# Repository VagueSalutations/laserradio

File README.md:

this is a test
If you can read this, Ian can access the repo

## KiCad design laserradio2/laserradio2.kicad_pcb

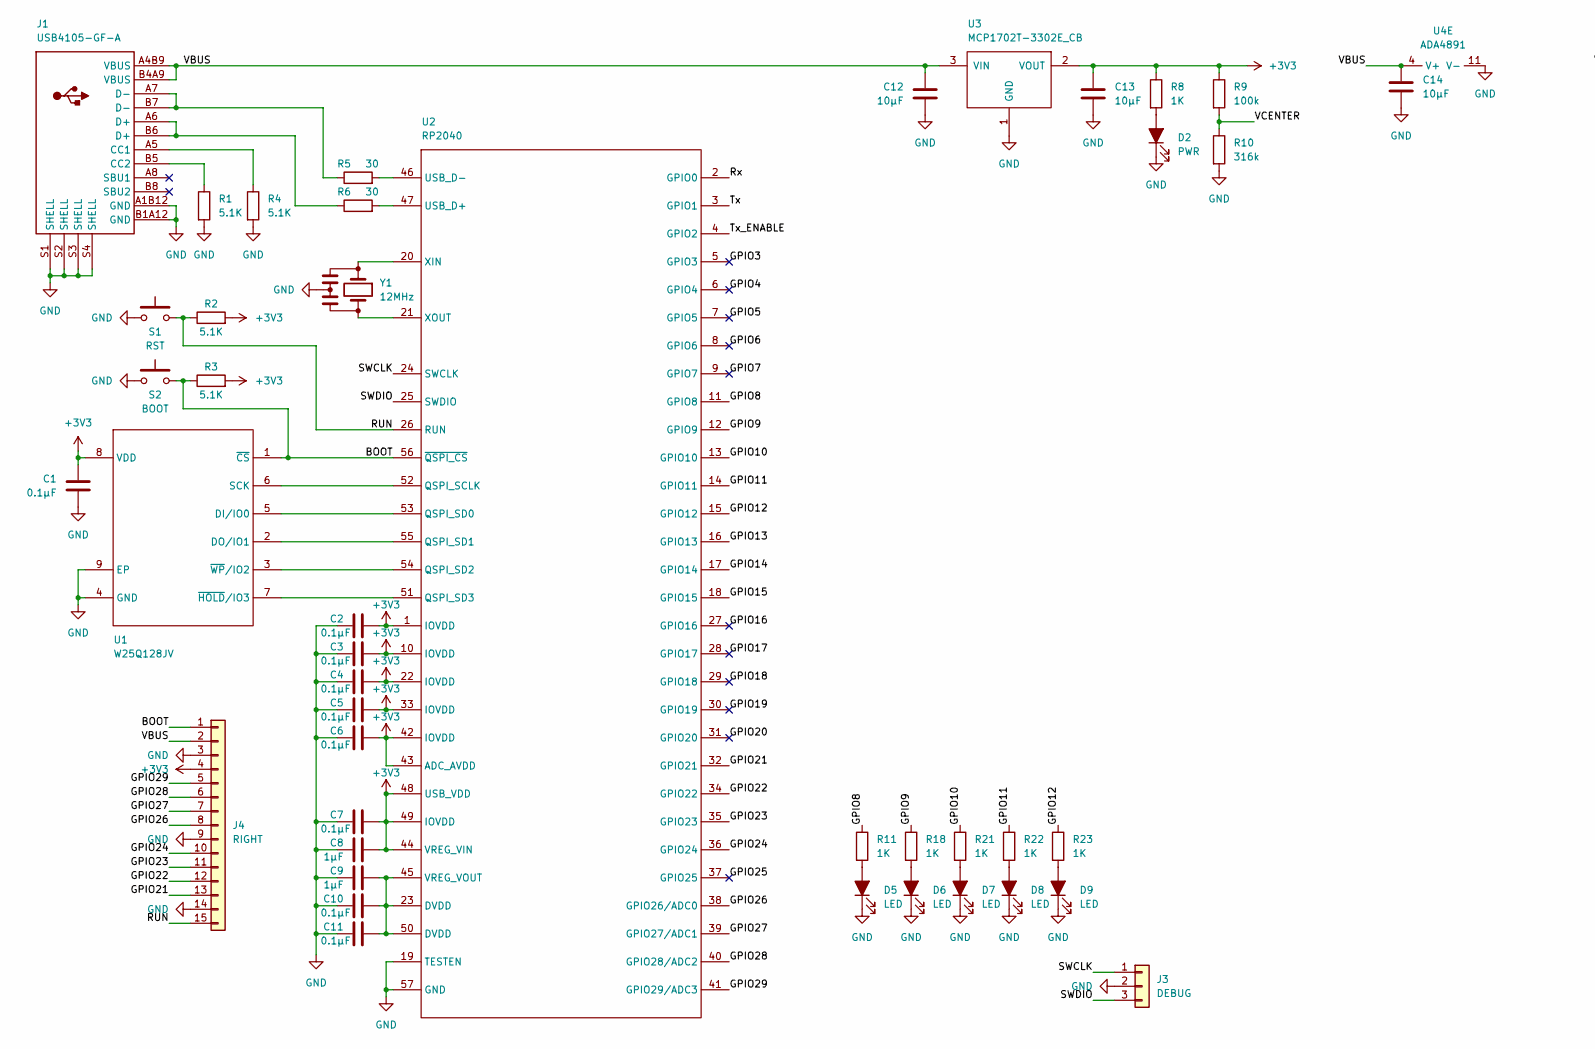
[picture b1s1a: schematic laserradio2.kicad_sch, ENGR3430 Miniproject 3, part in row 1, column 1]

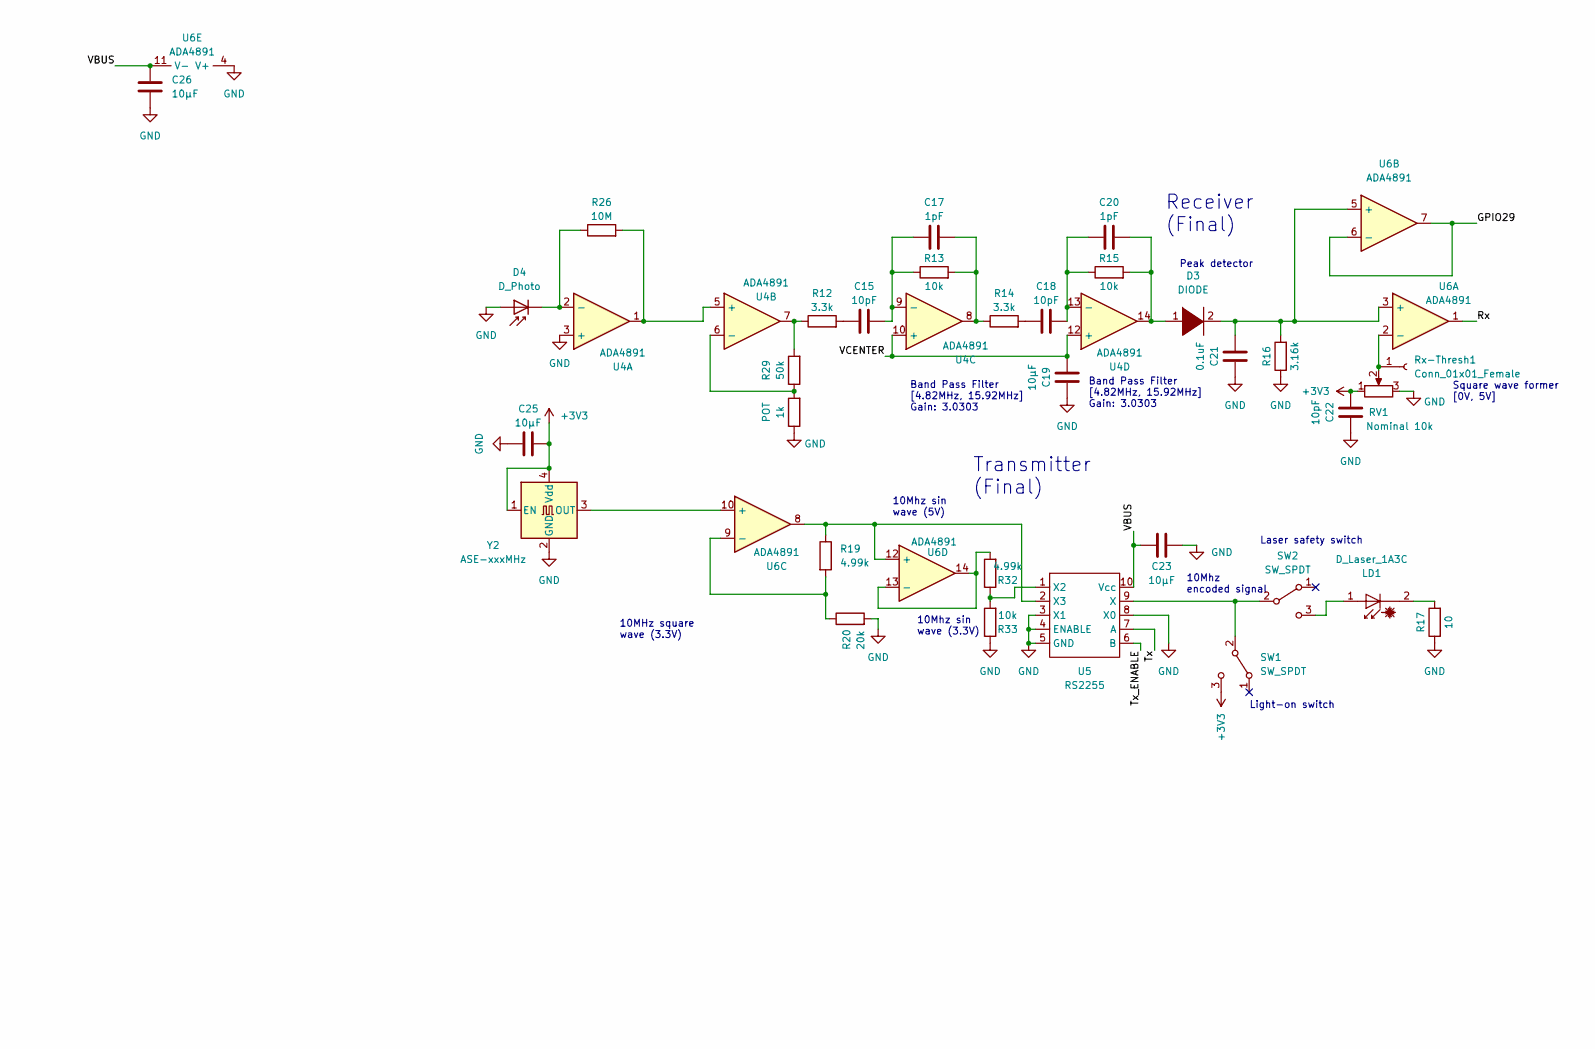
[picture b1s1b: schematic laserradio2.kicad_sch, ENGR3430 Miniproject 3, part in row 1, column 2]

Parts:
C1, C2, C3, C4, C5, C6, C7, C10, C11: 0.1µF; C_0603_1608Metric
C8, C9: 1µF; C_0603_1608Metric
C12, C13, C14, C19, C23, C25, C26: 10µF; C_0603_1608Metric
C15, C18, C22: 10pF; C_0603_1608Metric
C17, C20: 1pF; C_0603_1608Metric
C21: 0.1uF; C_0603_1608Metric
D2: PWR; LED_0805_2012Metric
D3: DIODE; D_SOD-123
D4: D_Photo; Laser_photodiode_2_pad
D5, D6, D7, D8, D9: LED; LED_0805_2012Metric
J1: USB4105-GF-A
J3: DEBUG; PinHeader_1x03_P2.54mm_Vertical
J4: RIGHT; PinHeader_1x15_P2.54mm_Vertical
LD1: D_Laser_1A3C; PinHeader_1x02_P2.54mm_Vertical
POT: 1k; R_0603_1608Metric
R1, R2, R3, R4: 5.1K; R_0603_1608Metric
R5, R6: 30; R_0603_1608Metric
R8, R11, R18, R21, R22, R23: 1K; R_0603_1608Metric
R9: 100k; R_0603_1608Metric
R10: 316k; R_0603_1608Metric
R12, R14: 3.3k; R_0603_1608Metric
R13, R15, R33: 10k; R_0603_1608Metric
R16: 3.16k; R_0603_1608Metric
R17: 10; R_0603_1608Metric
R19, R32: 4.99k; R_0603_1608Metric
R20: 20k; R_0603_1608Metric
R26: 10M; R_0603_1608Metric
R29: 50k; R_0603_1608Metric
RV1: Nominal 10k; Laser Potentiometer
Rx-Thresh1: Conn_01x01_Female; PinHeader_1x01_P2.54mm_Vertical
S1: RST; KXT321LHS
S2: BOOT; KXT321LHS
SW1, SW2: SW_SPDT; Laser Switch
U1: W25Q128JV; WSON-8-1EP_6x5mm_P1.27mm_EP3.4x4.3mm
U2: RP2040
U3: MCP1702T-3302E_CB; SOT-23
U4, U6: ADA4891; SOIC-14_3.9x8.7mm_P1.27mm
U5: RS2255; MSOP-10_3x3mm_P0.5mm
Y1: 12MHz; CSTNE
Y2: ASE-xxxMHz; Crystal_SMD_2520-4Pin_2.5x2.0mm

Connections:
+3V3: C1.2, C2.1, C3.1, C4.1, C5.1, C6.1, C7.1, C8.1, C13.1, C22.1, C25.1, J4.4, R2.2, R3.2, R8.1, R9.1, RV1.1, SW1.3 (C), U1.8 (VDD), U2.1 (IOVDD), U2.10 (IOVDD), U2.22 (IOVDD), U2.33 (IOVDD), U2.42 (IOVDD), U2.43 (ADC_AVDD), U2.44 (VREG_VIN), U2.48 (USB_VDD), U2.49 (IOVDD), U3.2 (VOUT), Y2.1 (EN), Y2.4 (Vdd); also elsewhere on the board
/BOOT: J4.1, R3.1, S2.2, U1.1 (~CS), U2.56 (~QSPI_CS)
/GPIO3: U2.5 (GPIO3)
/GPIO4: U2.6 (GPIO4)
/GPIO5: U2.7 (GPIO5)
/GPIO6: U2.8 (GPIO6)
/GPIO7: U2.9 (GPIO7)
/GPIO8: R11.1, U2.11 (GPIO8)
/GPIO9: R18.1, U2.12 (GPIO9)
/GPIO10: R21.1, U2.13 (GPIO10)
/GPIO11: R22.1, U2.14 (GPIO11)
/GPIO12: R23.1, U2.15 (GPIO12)
/GPIO13: U2.16 (GPIO13)
/GPIO14: U2.17 (GPIO14)
/GPIO15: U2.18 (GPIO15)
/GPIO16: U2.27 (GPIO16)
/GPIO17: U2.28 (GPIO17)
/GPIO18: U2.29 (GPIO18)
/GPIO19: U2.30 (GPIO19)
/GPIO20: U2.31 (GPIO20)
/GPIO21: J4.13, U2.32 (GPIO21)
/GPIO22: J4.12, U2.34 (GPIO22)
/GPIO23: J4.11, U2.35 (GPIO23)
/GPIO24: J4.10, U2.36 (GPIO24)
/GPIO25: U2.37 (GPIO25)
/GPIO26: J4.8, U2.38 (GPIO26/ADC0)
/GPIO27: J4.7, U2.39 (GPIO27/ADC1)
/GPIO28: J4.6, U2.40 (GPIO28/ADC2)
/GPIO29: J4.5, U2.41 (GPIO29/ADC3), U6.6 (-), U6.7
/RUN: J4.15, R2.1, S1.2, U2.26 (RUN)
/Rx: U2.2 (GPIO0), U6.1
/SWCLK: J3.1, U2.24 (SWCLK)
/SWDIO: J3.3, U2.25 (SWDIO)
/Tx: U2.3 (GPIO1), U5.7 (A)
/Tx_ENABLE: U2.4 (GPIO2), U5.6 (B)
/VBUS: C12.2, C14.1, C23.1, C26.1, J1.A4B9 (VBUS), J1.B4A9 (VBUS), J4.2, U3.3 (VIN), U4.4 (V+), U5.10 (Vcc), U6.11 (V-); also elsewhere on the board
/VCENTER: C19.1, R9.2, R10.1, U4.10 (+), U4.12 (+)
GND: C1.1, C2.2, C3.2, C4.2, C5.2, C6.2, C7.2, C8.2, C9.2, C10.2, C11.2, C12.1, C13.2, C14.2, C19.2, C21.2, C22.2, C23.2, C25.2, C26.2, D2.1 (K), D4.2 (A), D5.1 (K), D6.1 (K), D7.1 (K), D8.1 (K), D9.1 (K), J1.A1B12 (GND), J1.B1A12 (GND), J1.S1 (SHELL), J1.S2 (SHELL), J1.S3 (SHELL), J1.S4 (SHELL), J3.2, J4.3, J4.9, J4.14, POT.1, R1.2, R4.2, R10.2, R16.1, R17.1, R20.2, R33.1, RV1.3, S1.1, S2.1, U1.4 (GND), U1.9 (EP), U2.19 (TESTEN), U2.57 (GND), U3.1 (GND), U4.3 (+), U4.11 (V-), U5.3 (X1), U5.4 (ENABLE), U5.5 (GND), U5.8 (X0), U6.4 (V+), Y1.2, Y2.2 (GND); also elsewhere on the board
unnamed: C9.1, C10.1, C11.1, U2.23 (DVDD), U2.45 (VREG_VOUT), U2.50 (DVDD)
unnamed: C15.1, R12.2
unnamed: C15.2, C17.1, R13.1, U4.9 (-)
unnamed: C17.2, R13.2, R14.1, U4.8
unnamed: C18.1, R14.2
unnamed: C18.2, C20.1, R15.1, U4.13 (-)
unnamed: C20.2, D3.1 (K), R15.2, U4.14
unnamed: C21.1, D3.2 (A), R16.2, U6.3 (+), U6.5 (+)
unnamed: D2.2 (A), R8.2
unnamed 47: D4.1 (K), R26.1, U4.2 (-); also elsewhere on the board
unnamed: D5.2 (A), R11.2
unnamed: D6.2 (A), R18.2
unnamed: D7.2 (A), R21.2
unnamed: D8.2 (A), R22.2
unnamed: D9.2 (A), R23.2
unnamed: J1.A5 (CC1), R4.1
unnamed: J1.A6 (D+), J1.B6 (D+), R6.1
unnamed: J1.A7 (D-), J1.B7 (D-), R5.1
unnamed: J1.B5 (CC2), R1.1
unnamed: LD1.1 (A), SW2.3 (C)
unnamed: LD1.2 (K), R17.2
unnamed: R5.2, U2.46 (USB_D-)
unnamed: R6.2, U2.47 (USB_D+)
unnamed 61: R12.1, R29.2, U4.7; also elsewhere on the board
unnamed: R19.1, U5.2 (X3), U6.8, U6.12 (+)
unnamed 63: R19.2, R20.1, U6.9 (-); also elsewhere on the board
unnamed 65: R26.2, U4.1, U4.5 (+); also elsewhere on the board
unnamed 66: POT.2, R29.1, U4.6 (-); also elsewhere on the board
unnamed: R32.1, R33.2, U5.1 (X2)
unnamed: R32.2, U6.13 (-), U6.14
unnamed: RV1.2, Rx-Thresh1.1, U6.2 (-)
unnamed: SW1.2 (B), SW2.2 (B), U5.9 (X)
unnamed: U1.2 (DO/IO1), U2.55 (QSPI_SD1)
unnamed: U1.3 (~WP/IO2), U2.54 (QSPI_SD2)
unnamed: U1.5 (DI/IO0), U2.53 (QSPI_SD0)
unnamed: U1.6 (SCK), U2.52 (QSPI_SCLK)
unnamed: U1.7 (~HOLD/IO3), U2.51 (QSPI_SD3)
unnamed: U2.20 (XIN), Y1.1
unnamed: U2.21 (XOUT), Y1.3

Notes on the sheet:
Transmitter (Final)
Band Pass Filter [4.82MHz, 15.92MHz] Gain: 3.0303
Laser safety switch
Light-on switch
Receiver (Final)
Square wave former [0V, 5V]
Peak detector
10Mhz encoded signal
10Mhz sin wave (5V)
10MHz square wave (3.3V)
10Mhz sin wave (3.3V)

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
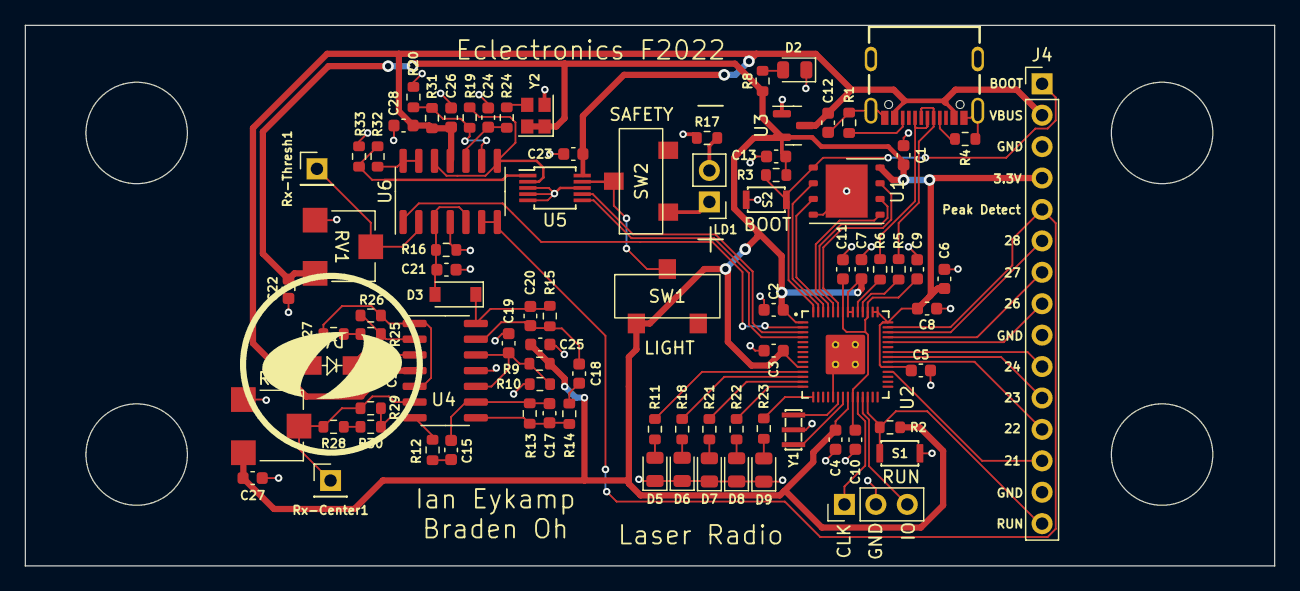
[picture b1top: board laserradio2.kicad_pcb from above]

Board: 2 copper layers, 101.0 x 43.7 mm, 88 parts (0 on the bottom side), 67 nets.

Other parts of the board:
C24, C27, C28: 10pF; C_0603_1608Metric
OlinLogoLg: G***; OlinLogoLg
R24: 1.1k; R_0603_1608Metric
R25, R27, R28, R30: 3.3k; R_0603_1608Metric
R31: 20k; R_0603_1608Metric
RV2: Nominal 10k; Laser Potentiometer
Rx-Center1: Conn_01x01_Female; PinHeader_1x01_P2.54mm_Vertical

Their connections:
+3V3: C27.1, RV2.1; also elsewhere on the board
/VBUS: C28.1, R31.1; also elsewhere on the board
GND: C24.2, C27.2, C28.2, RV2.3; also elsewhere on the board
unnamed 47: R25.1; also elsewhere on the board
unnamed 61: R30.2; also elsewhere on the board
unnamed 63: R31.2; also elsewhere on the board
unnamed: R25.2, R27.1
unnamed 65: R27.2; also elsewhere on the board
unnamed 66: R28.1, RV2.2, Rx-Center1.1; also elsewhere on the board
unnamed: R28.2, R30.1

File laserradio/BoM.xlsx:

laserradio
Ref | Value | Description | Vendor | Part Number | Per Board | Qty | PPU | Cost | Footprint
C1, C2, C3, C4, C5, C6, C7, C10, C11, | 0.1µF | Unpolarized capacitor | Stockroom | N/A | 9 | 36 |  | 0 | Capacitor_SMD:C_0603_1608Metric
C8, C9, | 1µF | Unpolarized capacitor | Stockroom | N/A | 2 | 8 |  | 0 | Capacitor_SMD:C_0603_1608Metric
C12, C13, C14, C19, C23, C25, C26, | 10µF | Unpolarized capacitor | Digikey | LMK107BBJ106KALT | 7 | 28 | 0.131 | 3.668 | Capacitor_SMD:C_0603_1608Metric
C15, C17, C18, C21, C22, C24, C27, C28, | 10pF | Unpolarized capacitor | Stockroom | N/A | 8 | 32 |  | 0 | Capacitor_SMD:C_0603_1608Metric
C20, | 1pF | Unpolarized capacitor | Digikey | 06035A1R0K4T2A | 1 | 4 | 0.53 | 2.12 | Capacitor_SMD:C_0603_1608Metric
D2, | PWR | LED, filled shape | Stockroom | N/A | 1 | 4 |  | 0 | LED_SMD:LED_0805_2012Metric
D3, | DIODE | Diode | Digikey | 1N5711W-7-F | 1 | 4 |  | 0 | Diode_SMD:D_SOD-123
D4, | D_Photo | Photodiode | Digikey | 040-101-411 | 1 | 4 | 1.85 | 7.4 | Eclectronics:Photodiode
D5, D6, D7, D8, D9, | LED | LED, filled shape | Stockroom | N/A | 5 | 20 |  | 0 | LED_SMD:LED_0805_2012Metric
J1, | USB4105-GF-A | USB C connector | Stockroom | N/A | 1 | 4 |  | 0 | Eclectronics:USB4105-GF-A
J3, | DEBUG | Generic, single row, 01x03 | N/A | N/A | 1 | 4 |  | 0 | Connector_PinHeader_2.54mm:PinHeader_1x03_P2.54mm_Vertical
J4, | RIGHT | Generic, single row, 01x15 | N/A | N/A | 1 | 4 |  | 0 | Connector_PinHeader_2.54mm:PinHeader_1x15_P2.54mm_Vertical
LD1, | D_Laser_1A3C | 650nm laser diode | Digikey | 1528-1391-ND | 1 | 4 | 5.95 | 23.8 | Connector_PinHeader_2.54mm:PinHeader_1x02_P2.54mm_Vertical
R1, R2, R3, R4, | 5.1K | Resistor | Digikey | RC0603FR-075K1L | 4 | 16 | 0.021 | 0.336 | Resistor_SMD:R_0603_1608Metric
R5, R6, | 30Ω | Resistor | Stockroom | N/A | 2 | 8 |  | 0 | Resistor_SMD:R_0603_1608Metric
R8, R11, R18, R21, R22, R23, | 1K | Resistor | Stockroom | N/A | 6 | 24 |  | 0 | Resistor_SMD:R_0603_1608Metric
R9, R16, | 100k | Resistor | Stockroom | N/A | 2 | 8 |  | 0 | Resistor_SMD:R_0603_1608Metric
R10, | 316k | Resistor | Stockroom | N/A | 1 | 4 |  | 0 | Resistor_SMD:R_0603_1608Metric
R12, R14, R25, R26, R27, R28, R29, R30, | 3.3k | Resistor | Digikey | RC0603FR-073K3L | 8 | 32 | 0.021 | 0.672 | Resistor_SMD:R_0603_1608Metric
R13, R17, | 1k | Resistor | Stockroom | N/A | 2 | 8 |  | 0 | Resistor_SMD:R_0603_1608Metric
R15, R33, | 10k | Resistor | Stockroom | N/A | 2 | 8 |  | 0 | Resistor_SMD:R_0603_1608Metric
R19, R32, | 4.99k | Resistor | Stockroom | N/A | 2 | 8 |  | 0 | Resistor_SMD:R_0603_1608Metric
R20, R31, | 20k | Resistor | Stockroom | N/A | 2 | 8 |  | 0 | Resistor_SMD:R_0603_1608Metric
R24, | 1.1k | Resistor | Stockroom | N/A | 1 | 4 |  | 0 | Resistor_SMD:R_0603_1608Metric
RV1, RV2, | Nominal 10k | 10k potentiometer | Digikey | PS6MH40-103A3030-PM | 2 | 8 | 1.05 | 8.4 | Eclectronics:Laser Potentiometer
Rx-Center1, | Conn_01x01_Female | Generic, single row, 01x01 | N/A | N/A | 1 | 4 |  | 0 | Connector_PinHeader_2.54mm:PinHeader_1x01_P2.54mm_Vertical
Rx-Thresh1, | Conn_01x01_Female | Generic, single row, 01x01 | N/A | N/A | 1 | 4 |  | 0 | Connector_PinHeader_2.54mm:PinHeader_1x01_P2.54mm_Vertical
S1, | RST | Switch, button | Stockroom | N/A | 1 | 4 |  | 0 | Eclectronics:KXT321LHS
S2, | BOOT | Switch, button | Stockroom | N/A | 1 | 4 |  | 0 | Eclectronics:KXT321LHS
SW1, SW2, | SW_SPDT | Switch, SPDT | Digikey | CL-SB-12B-01T | 2 | 8 | 0.87 | 6.96 | Eclectronics:Laser Switch
U1, | W25Q128JV | Flash memory | Stockroom | W25Q128JV | 1 | 4 |  | 0 | Package_SON:WSON-8-1EP_6x5mm_P1.27mm_EP3.4x4.3mm
U2, | RP2040 | RP2040 | Stockroom | RP2040 | 1 | 4 |  | 0 | Eclectronics:RP2040
U3, | MCP1702T-3302E_CB | Linear regulator | Stockroom | MCP1702T-3302E_CB | 1 | 4 |  | 0 | Package_TO_SOT_SMD:SOT-23
U4, U6, | ADA4891 | Quad op amp | Digikey | CLC4601ISO14X | 2 | 8 | 2.16 | 17.28 | Package_SO:SOIC-14_3.9x8.7mm_P1.27mm
U5, | RS2255 | IC MUX/DEMUX 4X1 | Digikey | RS2255XN | 1 | 4 | 0.6 | 2.4 | Package_SO:MSOP-10_3x3mm_P0.5mm
Y1, | 12MHz | 12MHz oscillator | Stockroom | N/A | 1 | 4 |  | 0 | Eclectronics:CSTNE
Y2, | 831061624 | WE-SPXO Oscillator | Digikey | 831061624 | 1 | 4 | 1.24 | 4.96 | Crystal:Crystal_SMD_2520-4Pin_2.5x2.0mm
 |  |  |  |  | Total Cost: |  |  | 77.996

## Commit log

2022-11-05 test commit
2022-11-06 Major push
2022-11-08 swap AD9833 (higher frequency DDS) for AD9837 (lower frequency)
2022-11-08 modify 10MHz generator circuit
2022-11-08 finish connecting pins on DDS
2022-11-08 Uploaded in-class work 11/08/22
2022-11-08 Added laser switches
2022-11-08 change switches and add annotations
2022-11-09 change crystal oscillator to 10MHz
2022-11-11 mid operation
2022-11-11 mid work
2022-11-11 Updated PCB file from schematic
2022-11-11 Fixed schematic bugs
2022-11-11 Fixed unconnected capacitor
2022-11-13 start layout of op-amp units
2022-11-13 wip arranging op-amp filters
2022-11-13 finish first pass of laying out components
2022-11-15 Refactored MP3 circuit
2022-11-15 fix voltage divider (adding extra op-amp buffer) on transmit side
2022-11-15 configure second amplifier to have variable gain
2022-11-16 update schematic
2022-11-16 Finalized schematic
2022-11-16 Mid work upload
2022-11-16 update footprint for swith with courtyard
2022-11-16 Major layout changes
2022-11-16 Major PCB changes
2022-11-16 Completed Initial Draft
2022-11-18 add plus and minus signs on laser diode
2022-11-18 prepare 3.3V and VBUS traces for enlargement
2022-11-18 increase power trace width
2022-11-18 increase via size on power traces
2022-11-18 fix DRC errors from overlapping too-close traces
2022-11-18 add mounting holes
2022-11-18 change resistor values to match what we have in stock
2022-11-18 Added BoM spreadsheet
2022-11-18 add photodiode footprint
2022-11-18 switch footprint for photodiode
2022-11-18 Finalized BoM
2022-11-18 add backup files
2022-12-03 add jig STL files
2022-12-05 Duplicated KiCAD project and added encoder.py
2022-12-21 add decoder script for hand-decoded message
2022-12-21 add LTspice files for op-amp simulation
2022-12-21 Pushed final files
